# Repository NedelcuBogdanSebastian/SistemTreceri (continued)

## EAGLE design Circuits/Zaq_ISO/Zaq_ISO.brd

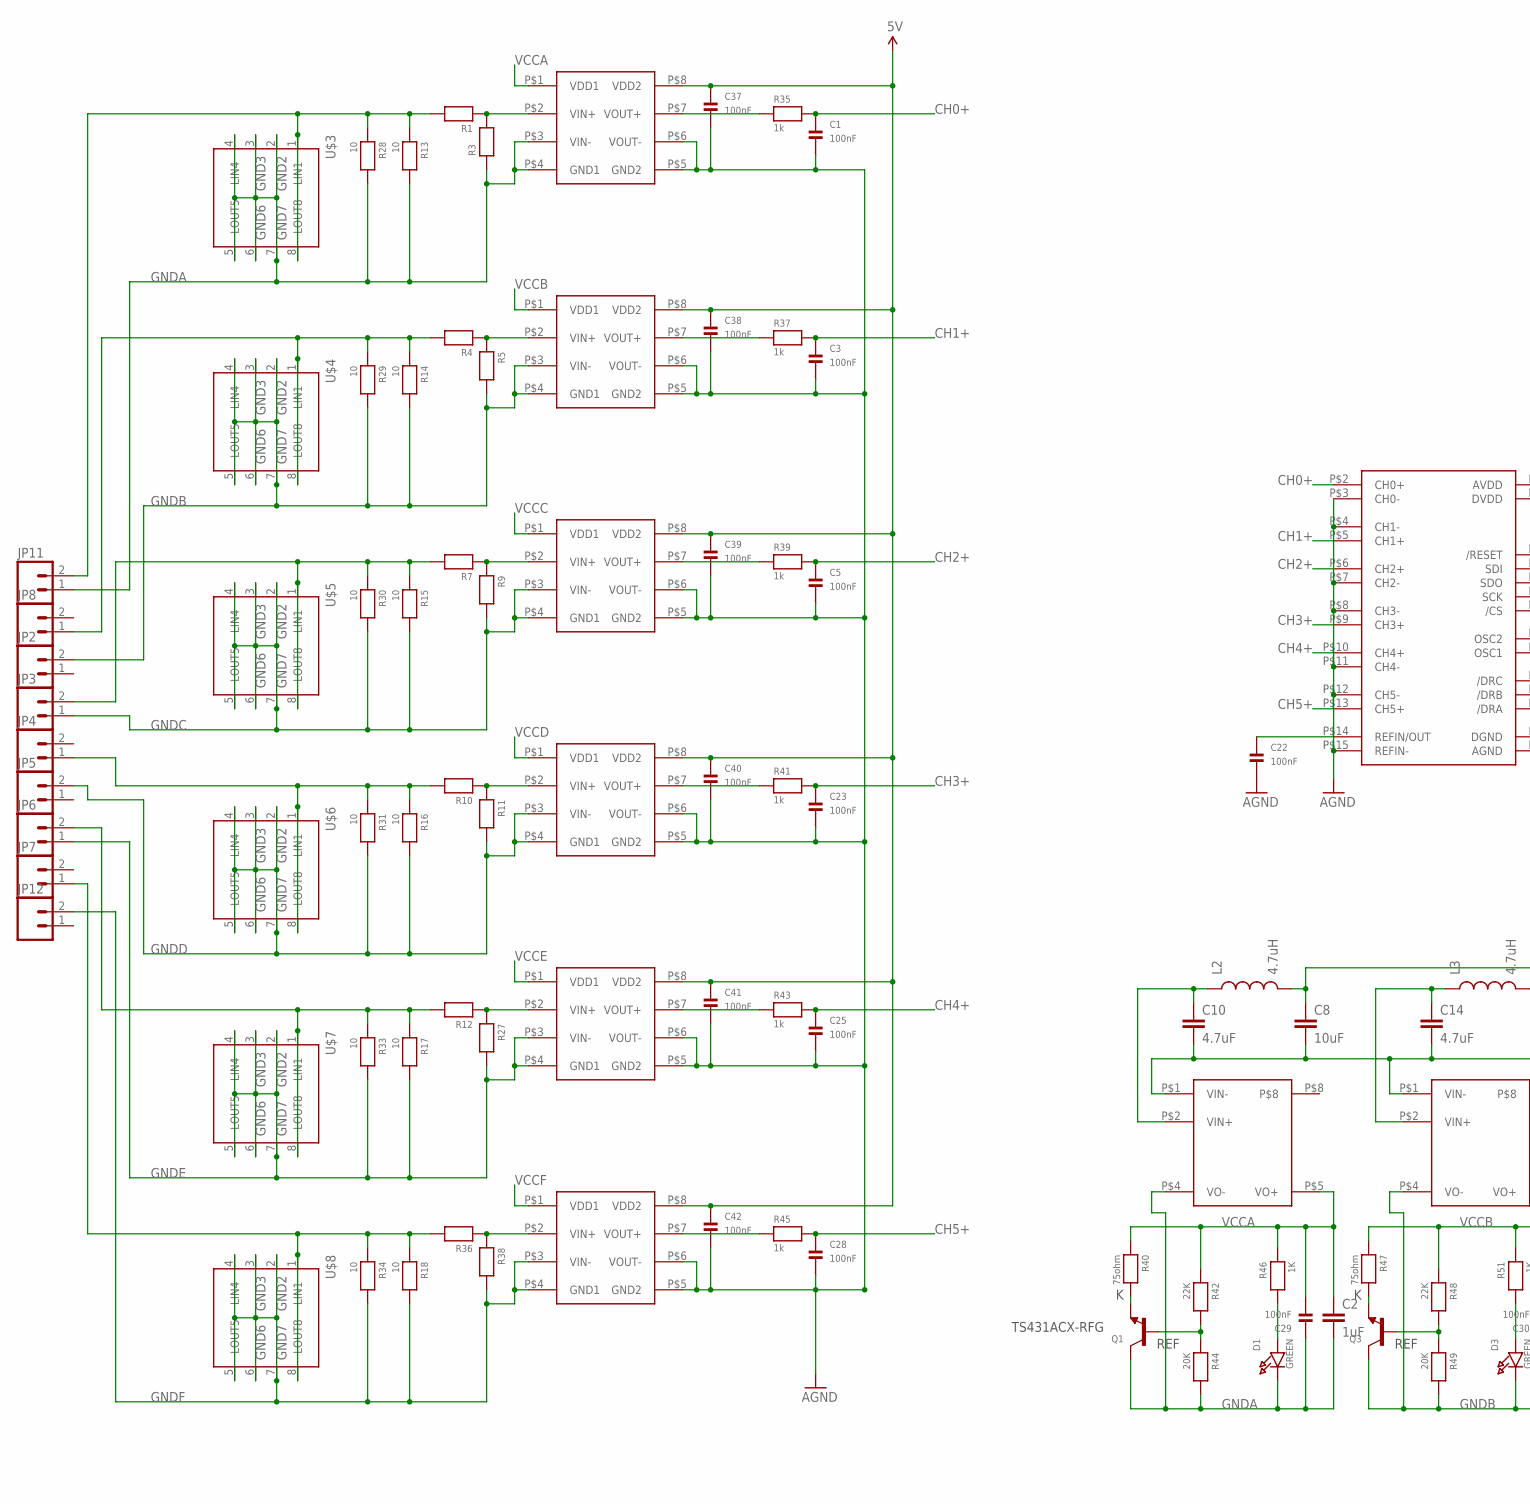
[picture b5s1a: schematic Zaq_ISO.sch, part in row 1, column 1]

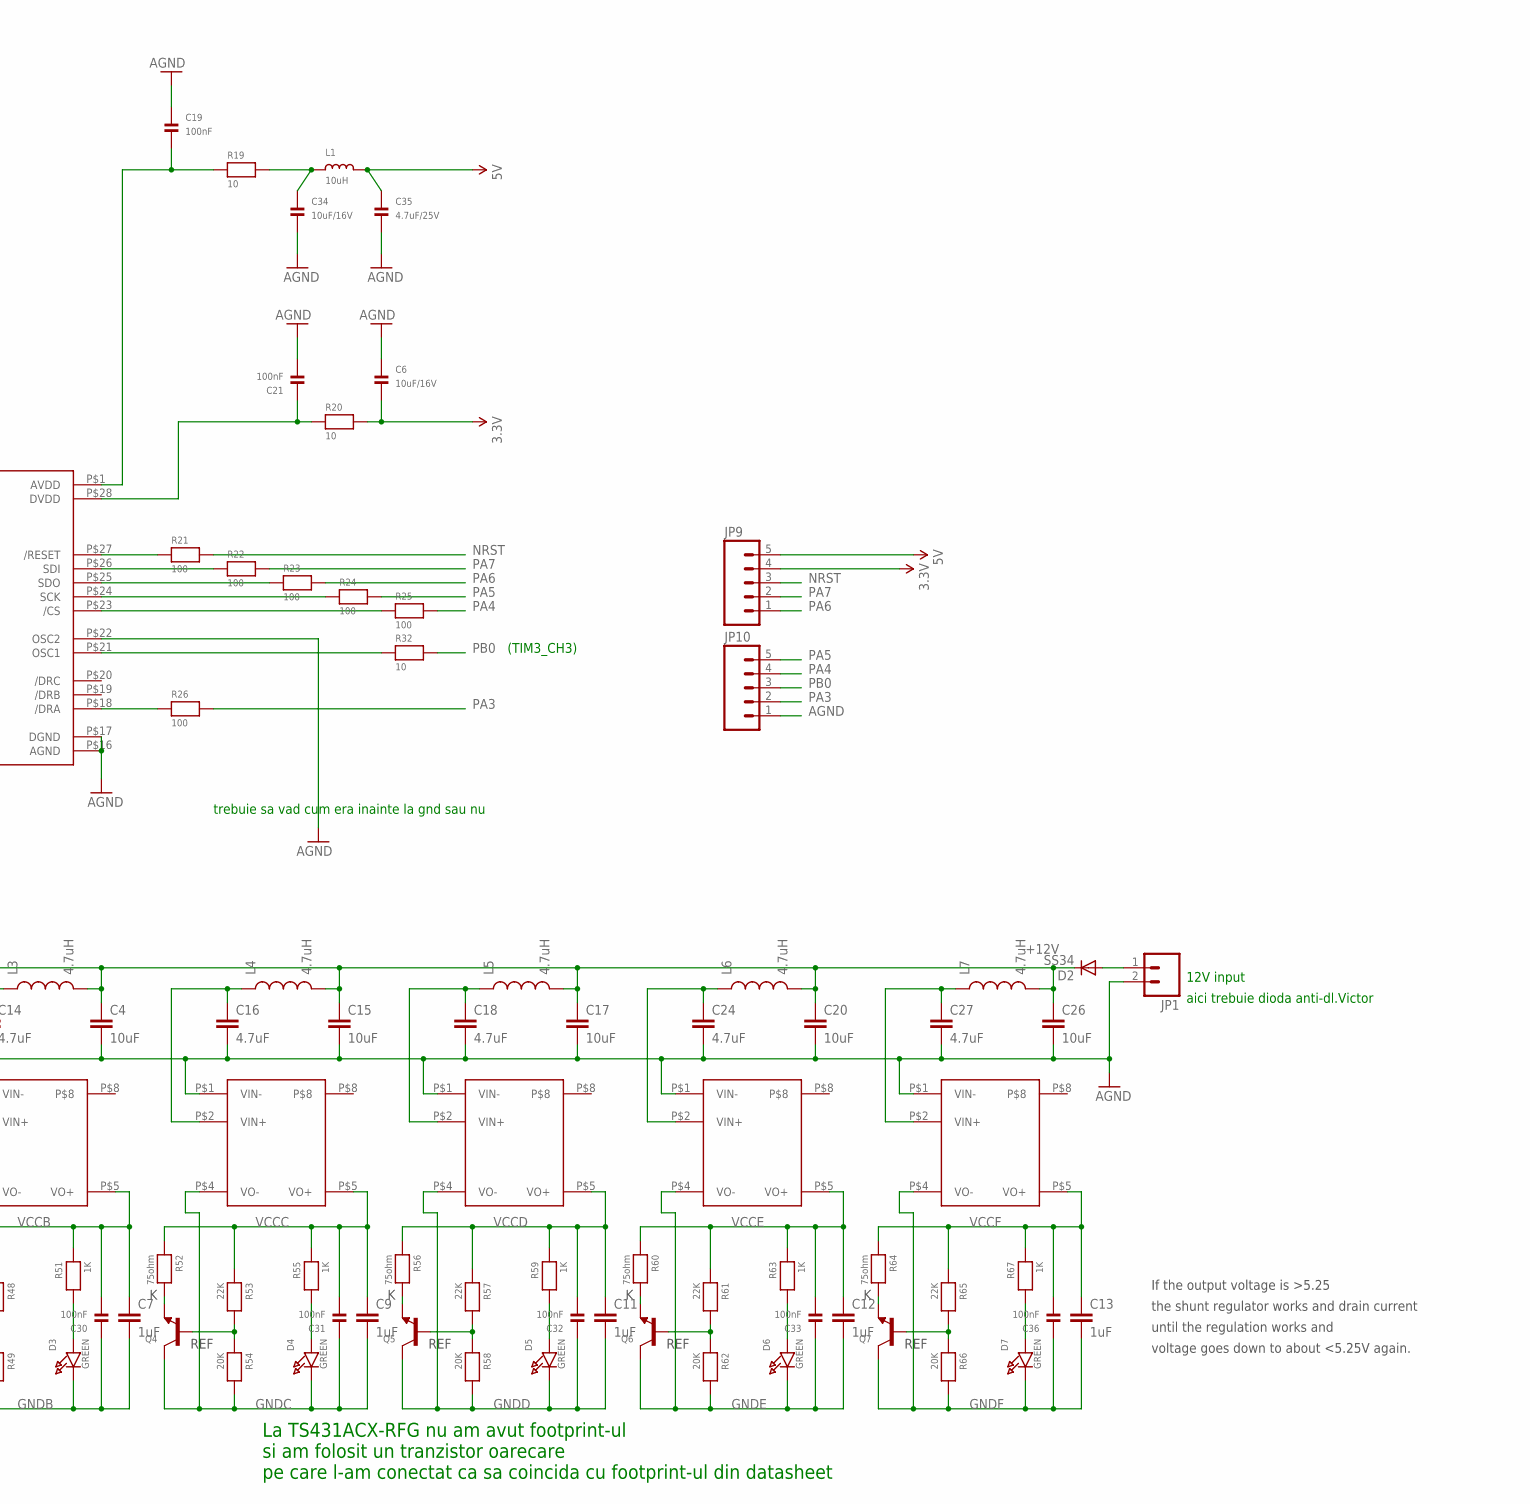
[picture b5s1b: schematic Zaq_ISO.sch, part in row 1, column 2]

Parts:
.: MCP3903; SSOP-28
C1, C3, C5, C19, C21, C22, C23, C25, C28, C29, C30, C31, C32, C33, C36, C37, C38, C39, C40, C41, C42: 100nF; _0805MP
C2, C7, C9, C11, C12, C13: 1uF; 1206
C4, C8, C15, C17, C20, C26: 10uF; 1206
C6, C34: 10uF/16V; _0805MP
C10, C14, C16, C18, C24, C27: 4.7uF; 1206
C35: 4.7uF/25V; _0805MP
D1, D3, D4, D5, D6, D7: GREEN; CHIPLED_0805_NOOUTLINE
D2: SS34; SMC
JP1, JP2, JP3, JP4, JP5, JP6, JP7, JP8, JP11, JP12: M025MM; SCREWTERMINAL-5MM-2
JP9, JP10: M05PTH_LONGPADS; 1X05_LONGPADS
L1: 10uH; _0805MP
L2, L3, L4, L5, L6, L7: 4.7uH; 1210
Q1, Q3, Q4, Q5, Q6, Q7: TRANSISTOR_NPNWAVE; SOT23-W
R1, R3, R4, R5, R7, R9, R10, R11, R12, R27, R36, R38: RESISTOR_0805MP; _0805MP
R13, R14, R15, R16, R17, R18, R28, R29, R30, R31, R33, R34: 10; 1206
R19, R20, R32: 10; _0805MP
R21, R22, R23, R24, R25, R26: 100; _0805MP
R35, R37, R39, R41, R43, R45: 1k; _0805MP
R40, R47, R52, R56, R60, R64: 75ohm; _0805MP
R42, R48, R53, R57, R61, R65: 22K; _0805MP
R44, R49, R54, R58, R62, R66: 20K; _0805MP
R46, R51, R55, R59, R63, R67: 1K; _0805MP
U$2, U$9, U$12, U$16, U$18, U$19: AMC1200SDUB; SOP
U$3, U$4, U$5, U$6, U$7, U$8: LC03_3V3; SO8
U$17, U$20, U$22, U$23, U$24, U$25: AM1LS-NJZ; AM1LS-JZ

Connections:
3.3V: C6.2, JP9.4, R20.2
5V: C35.1, C37.1, C38.1, C39.1, C40.1, C41.1, C42.1, JP9.5, L1.2, U$2.P$8 (VDD2), U$9.P$8 (VDD2), U$12.P$8 (VDD2), U$16.P$8 (VDD2), U$18.P$8 (VDD2), U$19.P$8 (VDD2)
+12V: C4.1, C8.1, C15.1, C17.1, C20.1, C26.1, D2.C, L2.2, L3.2, L4.2, L5.2, L6.2, L7.2
AGND: ..P$3 (CH0-), ..P$4 (CH1-), ..P$7 (CH2-), ..P$8 (CH3-), ..P$11 (CH4-), ..P$12 (CH5-), ..P$15 (REFIN-), ..P$16 (AGND), ..P$17 (DGND), ..P$22 (OSC2), C1.2, C3.2, C4.2, C5.2, C6.1, C8.2, C10.2, C14.2, C15.2, C16.2, C17.2, C18.2, C19.1, C20.2, C21.2, C22.2, C23.2, C24.2, C25.2, C26.2, C27.2, C28.2, C34.2, C35.2, C37.2, C38.2, C39.2, C40.2, C41.2, C42.2, JP1.2, JP10.1, U$2.P$5 (GND2), U$2.P$6 (VOUT-), U$9.P$5 (GND2), U$9.P$6 (VOUT-), U$12.P$5 (GND2), U$12.P$6 (VOUT-), U$16.P$5 (GND2), U$16.P$6 (VOUT-), U$17.P$1 (VIN-), U$18.P$5 (GND2), U$18.P$6 (VOUT-), U$19.P$5 (GND2), U$19.P$6 (VOUT-), U$20.P$1 (VIN-), U$22.P$1 (VIN-), U$23.P$1 (VIN-), U$24.P$1 (VIN-), U$25.P$1 (VIN-)
CH0+: ..P$2 (CH0+), C1.1, R35.2
CH1+: ..P$5 (CH1+), C3.1, R37.2
CH2+: ..P$6 (CH2+), C5.1, R39.2
CH3+: ..P$9 (CH3+), C23.1, R41.2
CH4+: ..P$10 (CH4+), C25.1, R43.2
CH5+: ..P$13 (CH5+), C28.1, R45.2
GNDA: C2.2, C29.1, D1.C, JP11.1, Q1.3 (C), R3.1, R13.2, R28.2, R44.2, U$2.P$3 (VIN-), U$2.P$4 (GND1), U$3.2 (GND_2), U$3.3 (GND_3), U$3.4 (LIN4), U$3.5 (LOUT5), U$3.6 (GND_6), U$3.7 (GND_7), U$17.P$4 (VO-)
GNDB: C7.2, C30.1, D3.C, JP2.2, Q3.3 (C), R5.2, R14.2, R29.2, R49.2, U$4.2 (GND_2), U$4.3 (GND_3), U$4.4 (LIN4), U$4.5 (LOUT5), U$4.6 (GND_6), U$4.7 (GND_7), U$9.P$3 (VIN-), U$9.P$4 (GND1), U$20.P$4 (VO-)
GNDC: C9.2, C31.1, D4.C, JP3.1, Q4.3 (C), R9.2, R15.2, R30.2, R54.2, U$5.2 (GND_2), U$5.3 (GND_3), U$5.4 (LIN4), U$5.5 (LOUT5), U$5.6 (GND_6), U$5.7 (GND_7), U$12.P$3 (VIN-), U$12.P$4 (GND1), U$22.P$4 (VO-)
GNDD: C11.2, C32.1, D5.C, JP5.2, Q5.3 (C), R11.2, R16.2, R31.2, R58.2, U$6.2 (GND_2), U$6.3 (GND_3), U$6.4 (LIN4), U$6.5 (LOUT5), U$6.6 (GND_6), U$6.7 (GND_7), U$16.P$3 (VIN-), U$16.P$4 (GND1), U$23.P$4 (VO-)
GNDE: C12.2, C33.1, D6.C, JP6.1, Q6.3 (C), R17.2, R27.2, R33.2, R62.2, U$7.2 (GND_2), U$7.3 (GND_3), U$7.4 (LIN4), U$7.5 (LOUT5), U$7.6 (GND_6), U$7.7 (GND_7), U$18.P$3 (VIN-), U$18.P$4 (GND1), U$24.P$4 (VO-)
GNDF: C13.2, C36.1, D7.C, JP12.2, Q7.3 (C), R18.2, R34.2, R38.2, R66.2, U$8.2 (GND_2), U$8.3 (GND_3), U$8.4 (LIN4), U$8.5 (LOUT5), U$8.6 (GND_6), U$8.7 (GND_7), U$19.P$3 (VIN-), U$19.P$4 (GND1), U$25.P$4 (VO-)
unnamed: ..P$21 (OSC1), R32.1
unnamed: ..P$1 (AVDD), C19.2, R19.1
unnamed: Q1.1 (B), R42.2, R44.1
unnamed: ..P$14 (REFIN/OUT), C22.1
unnamed: ..P$28 (DVDD), C21.1, R20.1
unnamed: ..P$27 (/RESET), R21.1
unnamed: ..P$26 (SDI), R22.1
unnamed: ..P$25 (SDO), R23.1
unnamed: ..P$24 (SCK), R24.1
unnamed: ..P$23 (/CS), R25.1
unnamed: ..P$18 (/DRA), R26.1
unnamed: Q1.2 (E), R40.2
unnamed: C14.1, L3.1, U$20.P$2 (VIN+)
unnamed: D1.A, R46.2
unnamed: R45.1, U$19.P$7 (VOUT+)
unnamed: R43.1, U$18.P$7 (VOUT+)
unnamed: R41.1, U$16.P$7 (VOUT+)
unnamed: R39.1, U$12.P$7 (VOUT+)
unnamed: C34.1, L1.1, R19.2
unnamed: R1.1, R3.2, U$2.P$2 (VIN+)
unnamed: R4.1, R5.1, U$9.P$2 (VIN+)
unnamed: R7.1, R9.1, U$12.P$2 (VIN+)
unnamed: R10.1, R11.1, U$16.P$2 (VIN+)
unnamed: R37.1, U$9.P$7 (VOUT+)
unnamed: R35.1, U$2.P$7 (VOUT+)
unnamed: Q3.1 (B), R48.2, R49.1
unnamed: Q3.2 (E), R47.2
unnamed: D3.A, R51.2
unnamed: R12.1, R27.1, U$18.P$2 (VIN+)
unnamed: R36.1, R38.1, U$19.P$2 (VIN+)
unnamed: Q4.1 (B), R53.2, R54.1
unnamed: Q4.2 (E), R52.2
unnamed: D4.A, R55.2
unnamed: D2.A, JP1.1
unnamed: Q5.1 (B), R57.2, R58.1
unnamed: Q5.2 (E), R56.2
unnamed: D5.A, R59.2
unnamed: JP7.1, R18.1, R34.1, R36.2, U$8.1 (LIN1), U$8.8 (LOUT8)
unnamed: JP6.2, R12.2, R17.1, R33.1, U$7.1 (LIN1), U$7.8 (LOUT8)
unnamed: JP4.1, R10.2, R16.1, R31.1, U$6.1 (LIN1), U$6.8 (LOUT8)
unnamed: Q6.1 (B), R61.2, R62.1
unnamed: Q6.2 (E), R60.2
unnamed: JP3.2, R7.2, R15.1, R30.1, U$5.1 (LIN1), U$5.8 (LOUT8)
unnamed: JP8.1, R4.2, R14.1, R29.1, U$4.1 (LIN1), U$4.8 (LOUT8)
unnamed: D6.A, R63.2
unnamed: JP11.2, R1.2, R13.1, R28.1, U$3.1 (LIN1), U$3.8 (LOUT8)
unnamed: Q7.1 (B), R65.2, R66.1
unnamed: Q7.2 (E), R64.2
unnamed: D7.A, R67.2
unnamed: C27.1, L7.1, U$25.P$2 (VIN+)
unnamed: C24.1, L6.1, U$24.P$2 (VIN+)
unnamed: C18.1, L5.1, U$23.P$2 (VIN+)
unnamed: C10.1, L2.1, U$17.P$2 (VIN+)
unnamed: C16.1, L4.1, U$22.P$2 (VIN+)
NRST: JP9.3, R21.2
PA3: JP10.2, R26.2
PA4: JP10.4, R25.2
PA5: JP10.5, R24.2
PA6: JP9.1, R23.2
PA7: JP9.2, R22.2
PB0: JP10.3, R32.2
VCCA: C2.1, C29.2, R40.1, R42.1, R46.1, U$2.P$1 (VDD1), U$17.P$5 (VO+)
VCCB: C7.1, C30.2, R47.1, R48.1, R51.1, U$9.P$1 (VDD1), U$20.P$5 (VO+)
VCCC: C9.1, C31.2, R52.1, R53.1, R55.1, U$12.P$1 (VDD1), U$22.P$5 (VO+)
VCCD: C11.1, C32.2, R56.1, R57.1, R59.1, U$16.P$1 (VDD1), U$23.P$5 (VO+)
VCCE: C12.1, C33.2, R60.1, R61.1, R63.1, U$18.P$1 (VDD1), U$24.P$5 (VO+)
VCCF: C13.1, C36.2, R64.1, R65.1, R67.1, U$19.P$1 (VDD1), U$25.P$5 (VO+)

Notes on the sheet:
(TIM3_CH3)
trebuie sa vad cum era inainte la gnd sau nu
If the output voltage is >5.25
the shunt regulator works and drain current
until the regulation works and
voltage goes down to about <5.25V again.
REF
TS431ACX-RFG
La TS431ACX-RFG nu am avut footprint-ul
si am folosit un tranzistor oarecare
12V input
aici trebuie dioda anti-dl.Victor
pe care l-am conectat ca sa coincida cu footprint-ul din datasheet

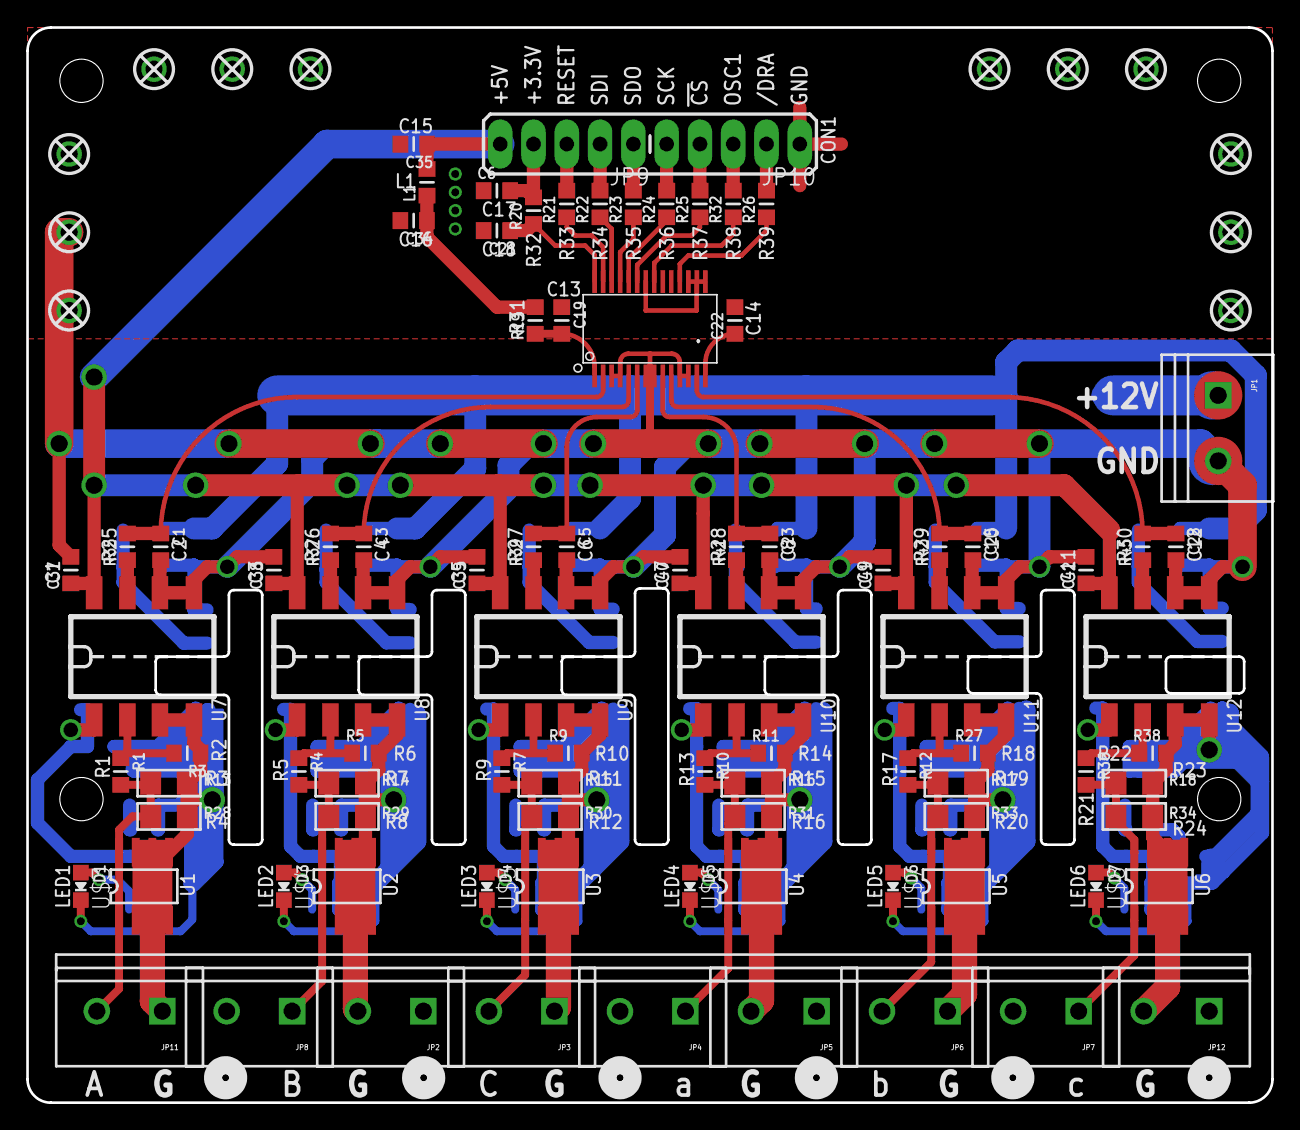
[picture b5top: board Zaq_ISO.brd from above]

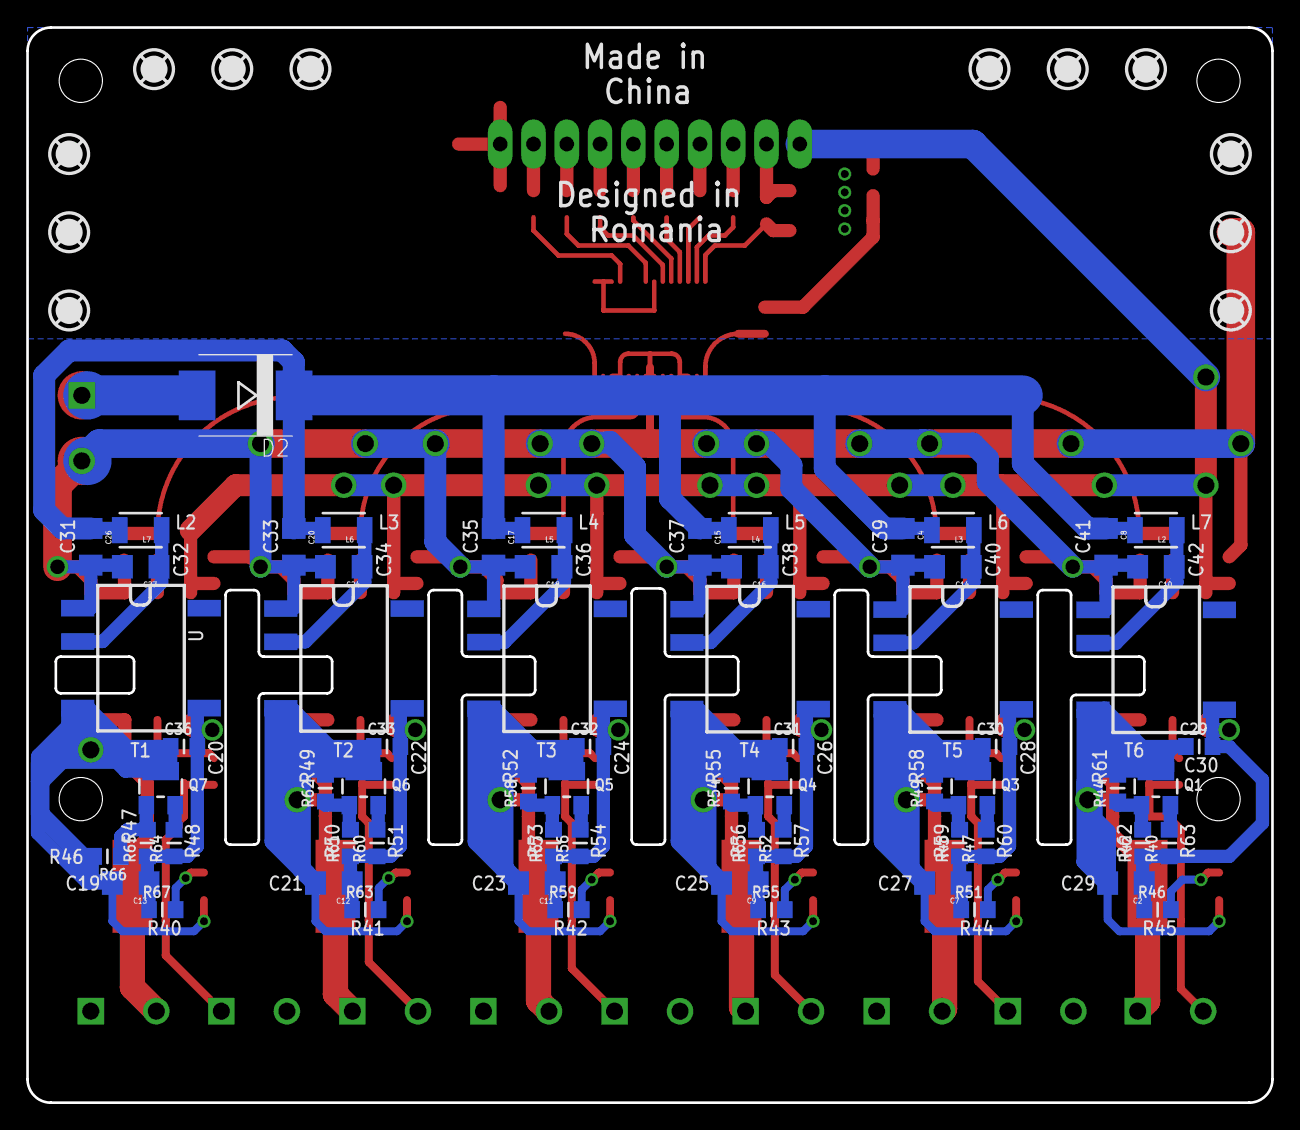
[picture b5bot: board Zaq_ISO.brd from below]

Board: 2 copper layers, 95.0 x 82.0 mm, 160 parts (67 on the bottom side), 83 nets.

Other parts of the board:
STANDOFF1, STANDOFF6, STANDOFF10, STANDOFF12: STAND-OFF

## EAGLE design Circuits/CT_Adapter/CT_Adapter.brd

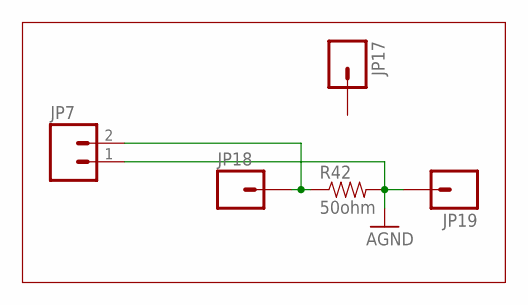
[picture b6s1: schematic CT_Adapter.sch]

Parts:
JP7: M025MM; SCREWTERMINAL-5MM-2
JP17, JP18, JP19: M01PTH_LONGPAD; 1X01_LONGPAD
R42: 50ohm; 1206

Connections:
AGND: JP7.1, JP19.1, R42.2
unnamed: JP7.2, JP18.1, R42.1

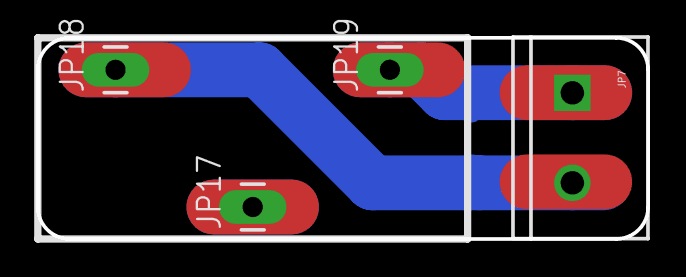
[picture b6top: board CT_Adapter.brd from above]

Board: 2 copper layers, 33.9 x 11.2 mm, 5 parts (1 on the bottom side), 2 nets.

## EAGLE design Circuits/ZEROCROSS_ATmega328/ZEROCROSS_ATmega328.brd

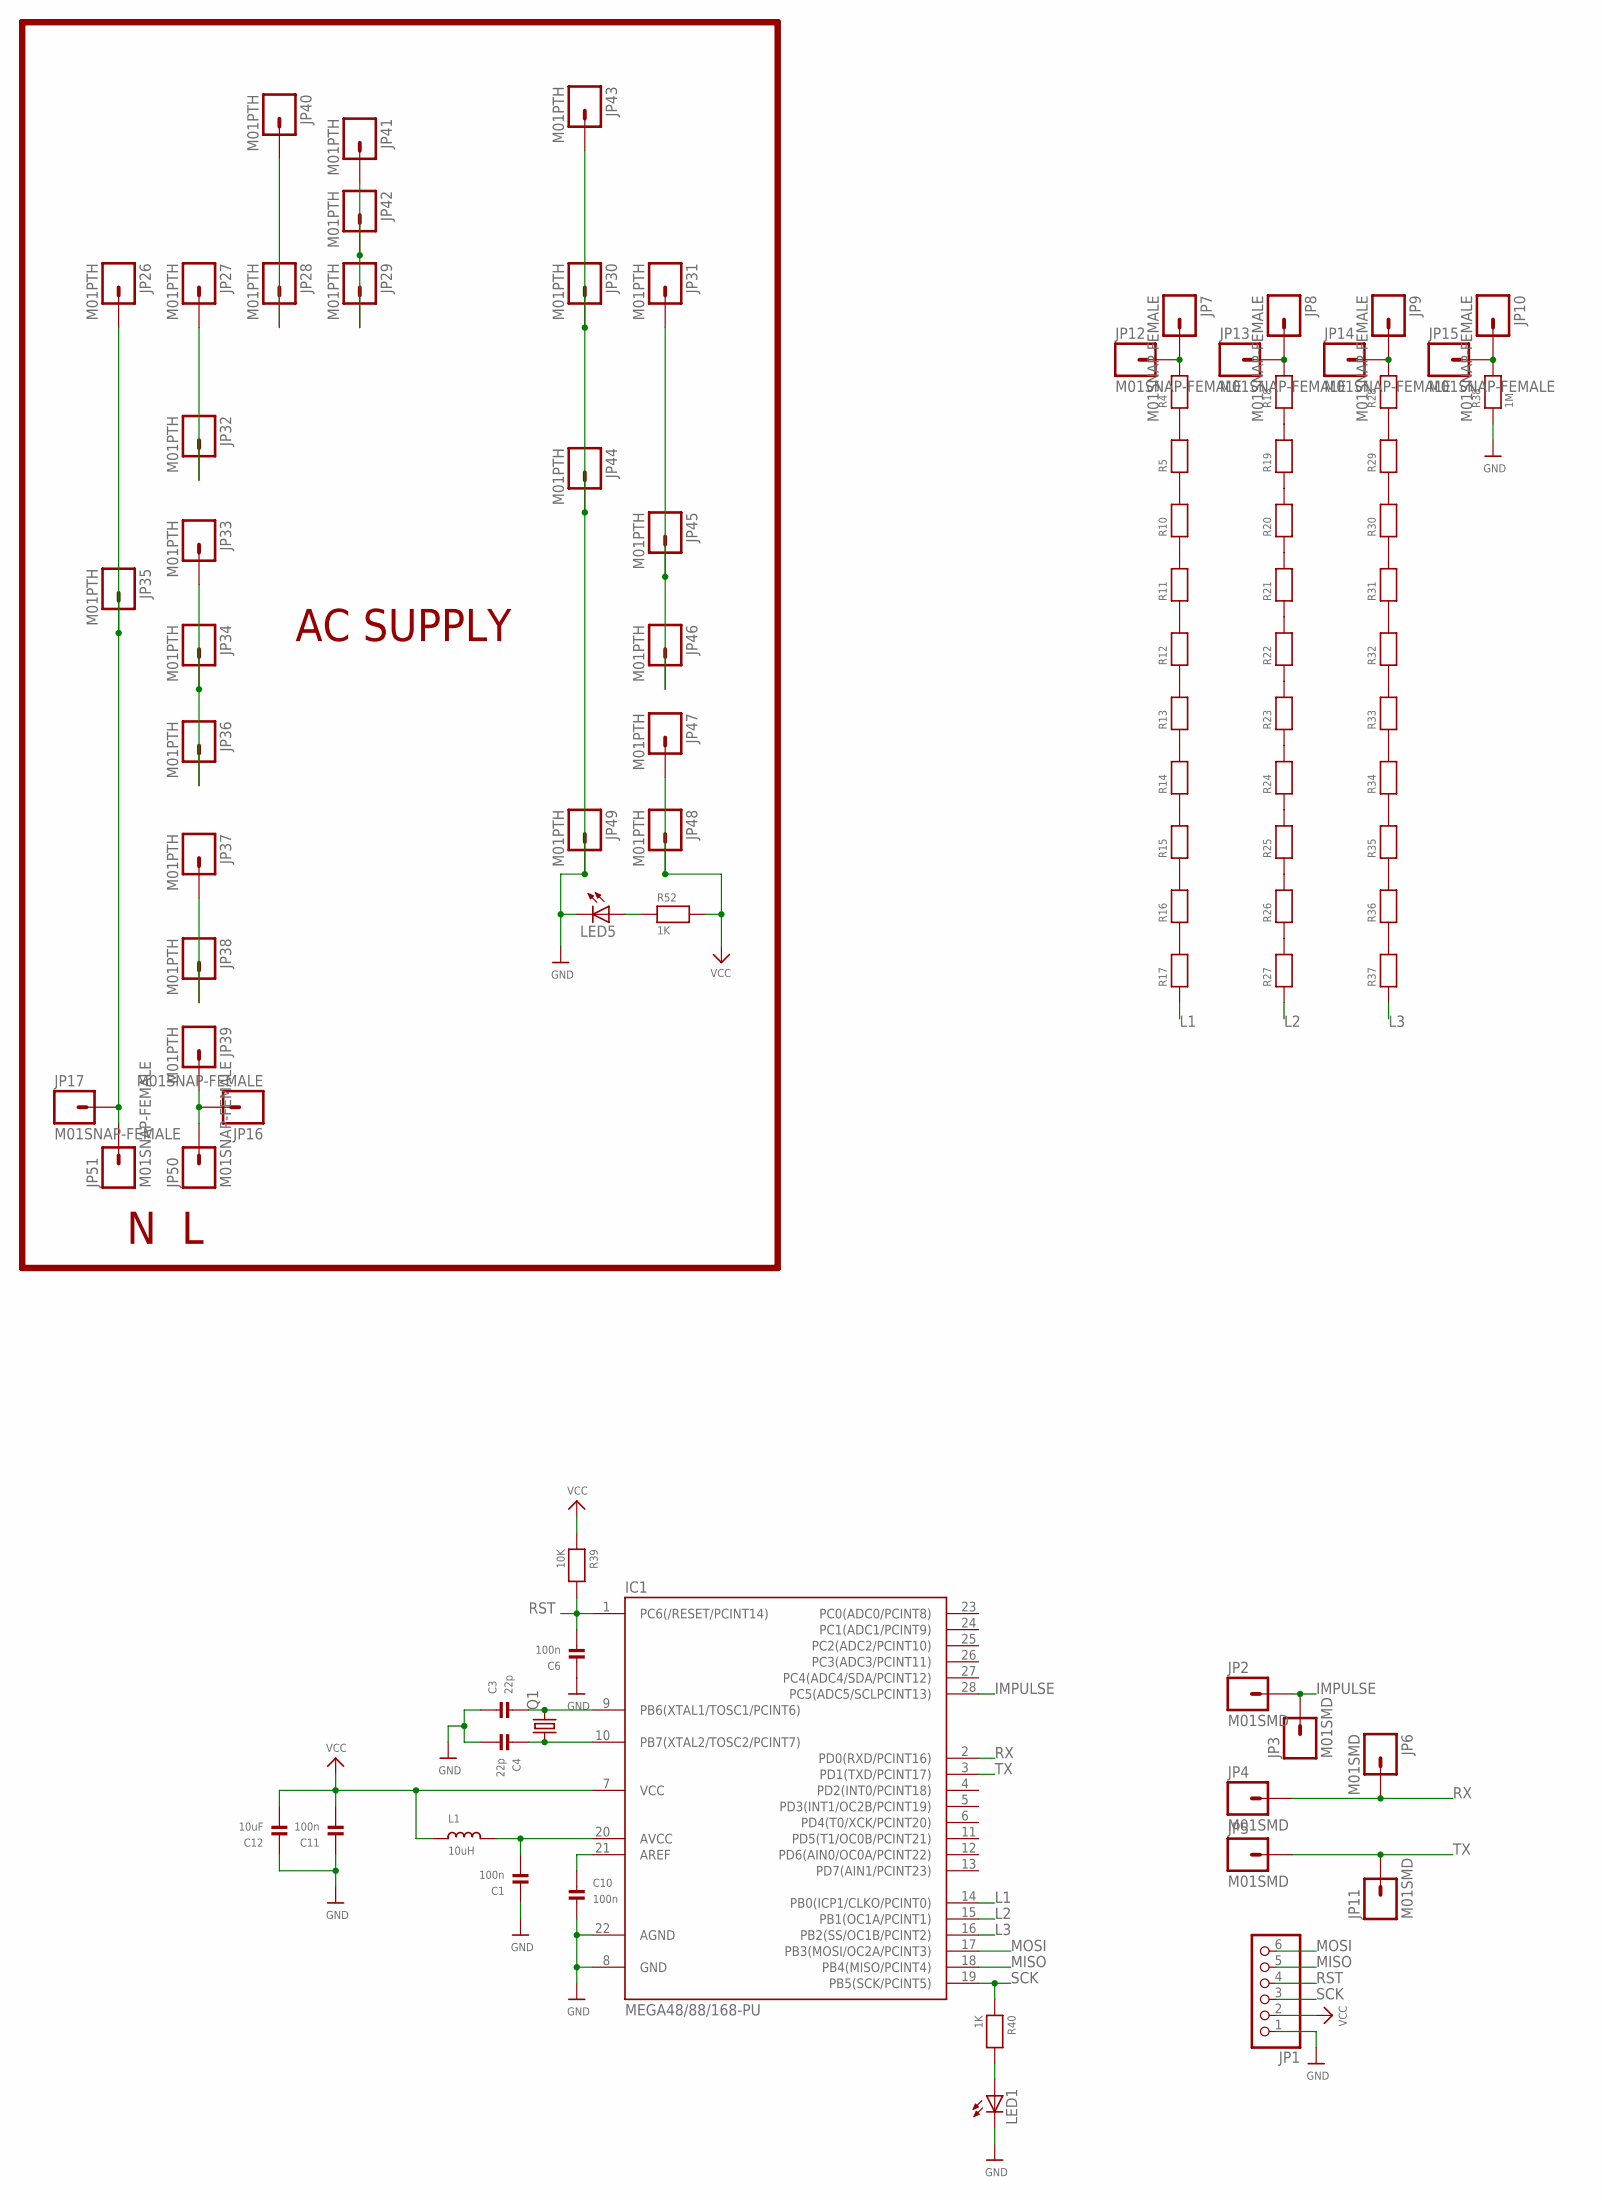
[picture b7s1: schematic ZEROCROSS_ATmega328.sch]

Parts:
C1, C6, C10, C11: 100n; _0805MP
C3, C4: 22p; _0805MP
C12: 10uF; _0805MP
IC1: MEGA48/88/168-PU; DIL28-3
JP1: HEADER-1X6; 1X06_OVAL
JP2, JP3, JP4, JP5, JP6, JP11: M01SMD; LUXEON-PAD
JP7, JP8, JP9, JP10, JP12, JP13, JP14, JP15, JP16, JP17, JP50, JP51: M01SNAP-FEMALE; SNAP-FEMALE
JP26, JP27, JP28, JP29, JP30, JP31, JP32, JP33, JP34, JP35, JP36, JP37, JP38, JP39, JP40, JP41, JP42, JP43, JP44, JP45, JP46, JP47, JP48, JP49: M01PTH; 1X01
L1: 10uH; _0805MP
LED1, LED5: LED-3MM-NO_SILK; LED3MM-NS
Q1: CRYSTALHC49U-V; HC49U-V
R4, R5, R10, R11, R12, R13, R14, R15, R16, R17, R18, R19, R20, R21, R22, R23, R24, R25, R26, R27, R28, R29, R30, R31, R32, R33, R34, R35, R36, R37: RESISTOR1206; 1206
R38: 1M; 1206
R39: 10K; _0805MP
R40, R52: 1K; _0805MP

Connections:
IMPULSE: IC1.28 (PC5(ADC5/SCLPCINT13)), JP2.P$1, JP3.P$1
L1: IC1.14 (PB0(ICP1/CLKO/PCINT0)), R17.1
L2: IC1.15 (PB1(OC1A/PCINT1)), R27.1
L3: IC1.16 (PB2(SS/OC1B/PCINT2)), R37.1
MISO: IC1.18 (PB4(MISO/PCINT4)), JP1.5
MOSI: IC1.17 (PB3(MOSI/OC2A/PCINT3)), JP1.6
unnamed: C1.2, IC1.20 (AVCC), L1.2
unnamed: C11.2, C12.2, IC1.7 (VCC), JP1.2, JP47.1, JP48.1, L1.1, R39.1, R52.2
unnamed: R4.1, R5.2
unnamed: R5.1, R10.2
unnamed: R10.1, R11.2
unnamed: R11.1, R12.2
unnamed: R12.1, R13.2
unnamed: R13.1, R14.2
unnamed: R14.1, R15.2
unnamed: R15.1, R16.2
unnamed: R16.1, R17.2
unnamed: R18.1, R19.2
unnamed: R19.1, R20.2
unnamed: R20.1, R21.2
unnamed: R21.1, R22.2
unnamed: R22.1, R23.2
unnamed: R23.1, R24.2
unnamed: R24.1, R25.2
unnamed: R25.1, R26.2
unnamed: R26.1, R27.2
unnamed: R28.1, R29.2
unnamed: R29.1, R30.2
unnamed: R30.1, R31.2
unnamed: R31.1, R32.2
unnamed: R32.1, R33.2
unnamed: R33.1, R34.2
unnamed: R34.1, R35.2
unnamed: R35.1, R36.2
unnamed: R36.1, R37.2
unnamed: C3.2, IC1.9 (PB6(XTAL1/TOSC1/PCINT6)), Q1.2
unnamed: C4.1, IC1.10 (PB7(XTAL2/TOSC2/PCINT7)), Q1.1
unnamed: C10.1, IC1.21 (AREF)
unnamed: C1.1, C3.1, C4.2, C6.1, C10.2, C11.1, C12.1, IC1.8 (GND), IC1.22 (AGND), JP1.1, JP30.1, JP43.1, JP44.1, JP49.1, LED1.K (C), LED5.K (C), R38.1
unnamed: JP7.1, JP12.1, R4.2
unnamed: JP8.1, JP13.1, R18.2
unnamed: JP9.1, JP14.1, R28.2
unnamed: JP10.1, JP15.1, R38.2
unnamed: LED1.A, R40.2
unnamed: JP17.1, JP26.1, JP35.1, JP51.1
unnamed: JP27.1, JP32.1
unnamed: JP33.1, JP34.1, JP36.1
unnamed: JP37.1, JP38.1
unnamed: JP16.1, JP39.1, JP50.1
unnamed: JP28.1, JP40.1
unnamed: JP29.1, JP41.1, JP42.1
unnamed: JP31.1, JP45.1, JP46.1
unnamed: LED5.A, R52.1
RST: C6.2, IC1.1 (PC6(/RESET/PCINT14)), JP1.4, R39.2
RX: IC1.2 (PD0(RXD/PCINT16)), JP4.P$1, JP6.P$1
SCK: IC1.19 (PB5(SCK/PCINT5)), JP1.3, R40.1
TX: IC1.3 (PD1(TXD/PCINT17)), JP5.P$1, JP11.P$1

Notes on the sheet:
N L
AC SUPPLY

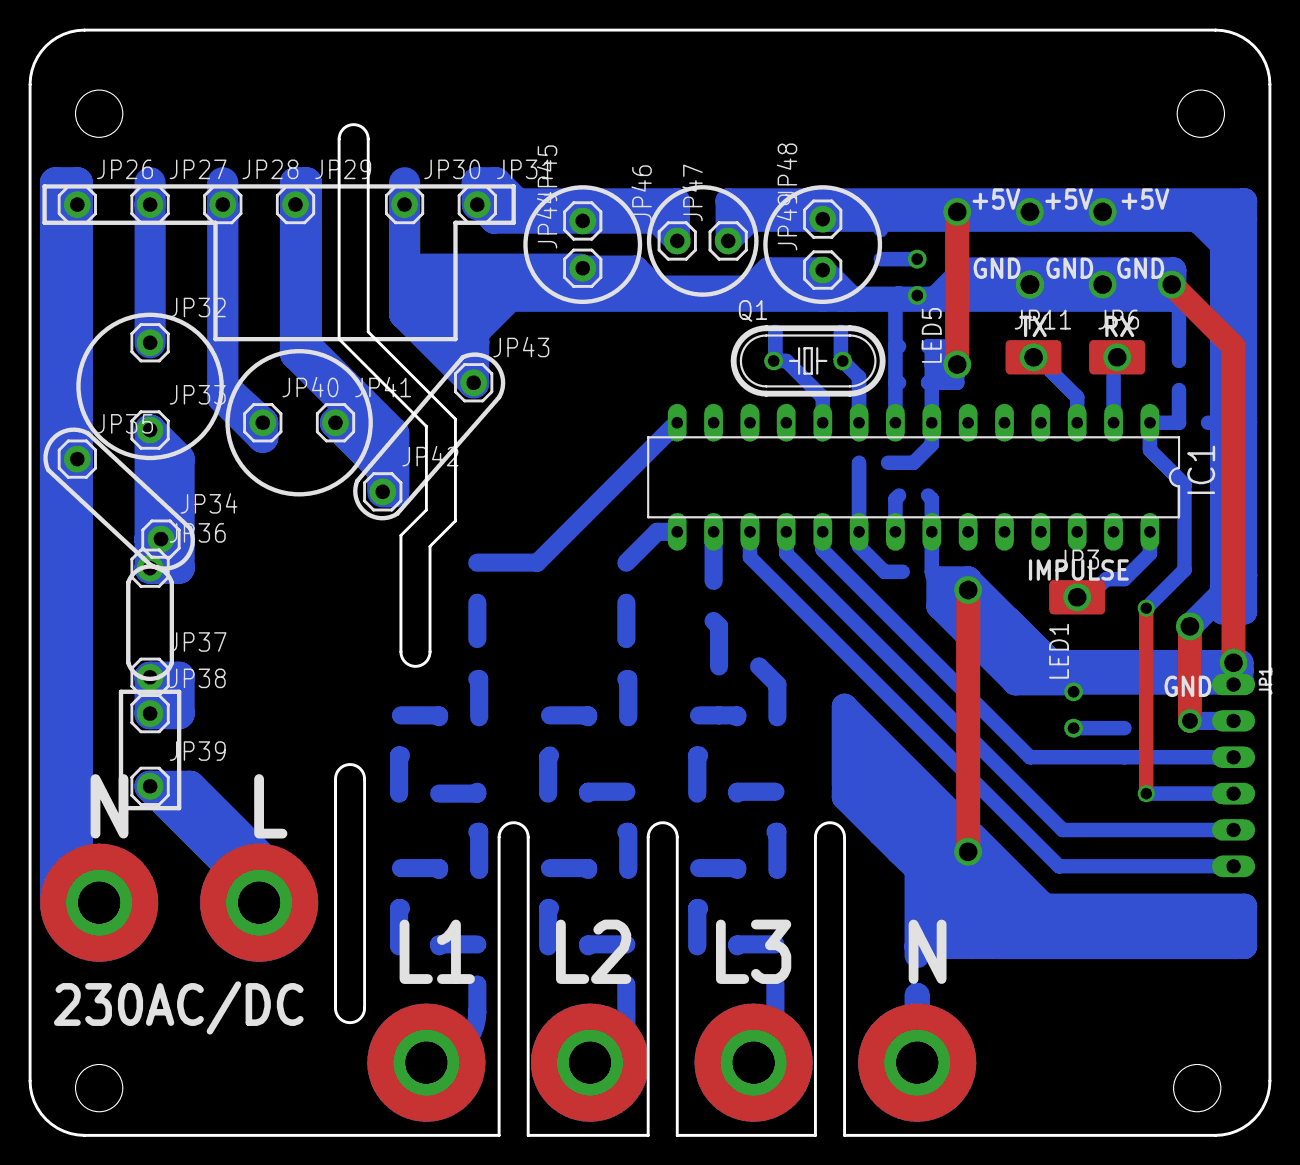
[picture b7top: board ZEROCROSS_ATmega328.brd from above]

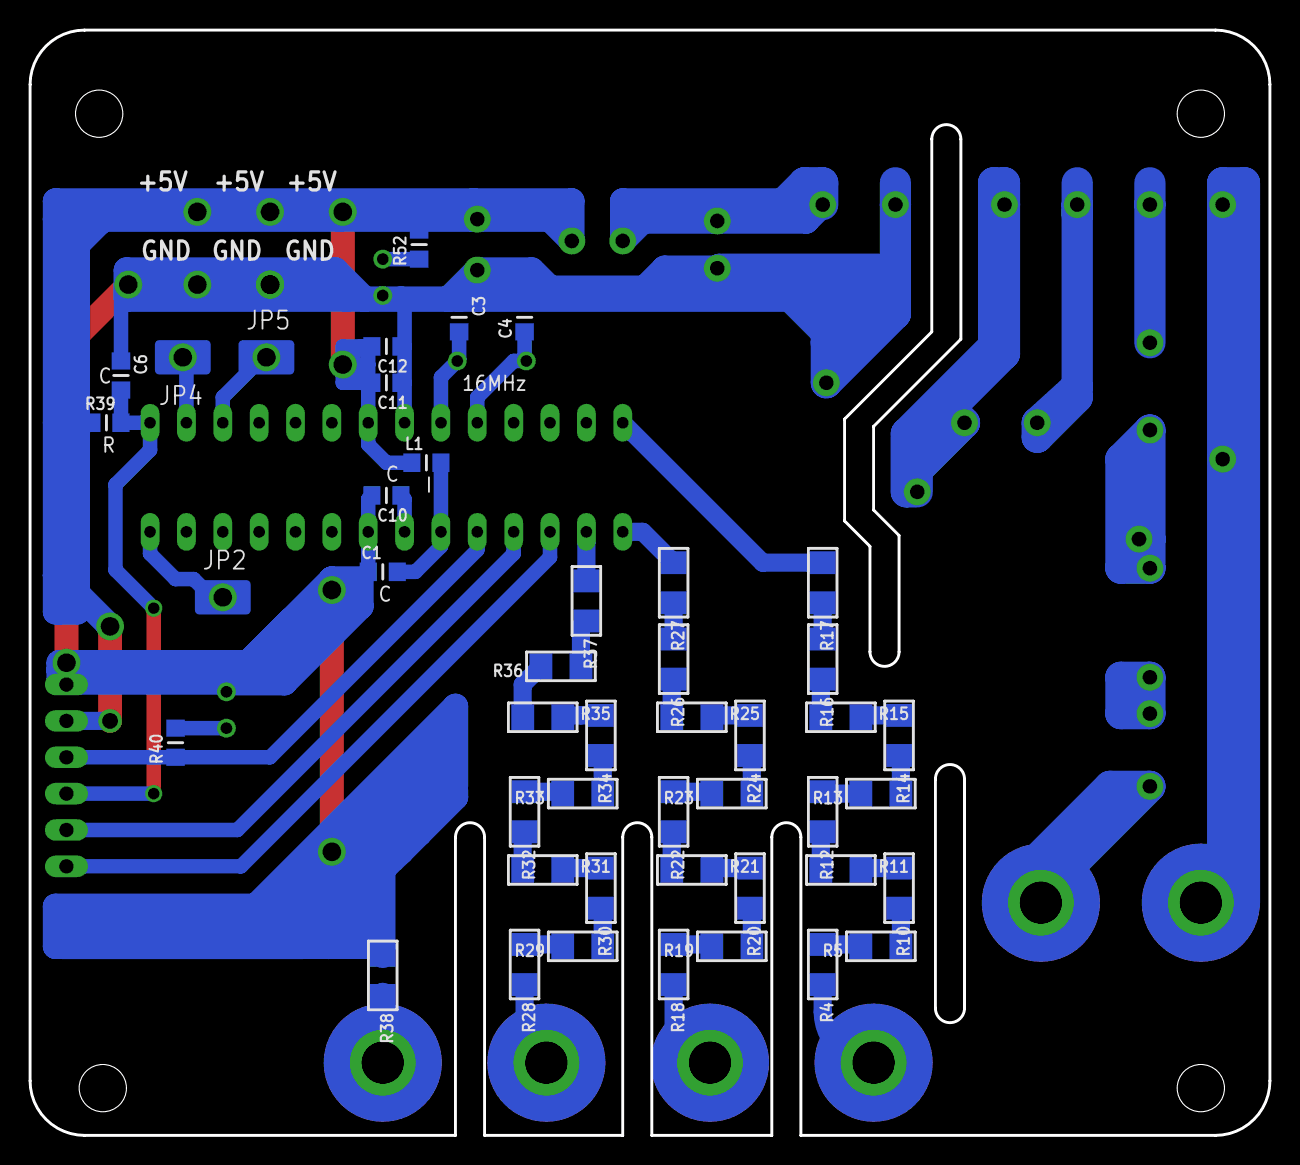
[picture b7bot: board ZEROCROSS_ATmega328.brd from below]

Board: 2 copper layers, 86.6 x 77.2 mm, 93 parts (51 on the bottom side), 57 nets.

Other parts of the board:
STANDOFF1, STANDOFF2, STANDOFF3, STANDOFF4: STAND-OFF
